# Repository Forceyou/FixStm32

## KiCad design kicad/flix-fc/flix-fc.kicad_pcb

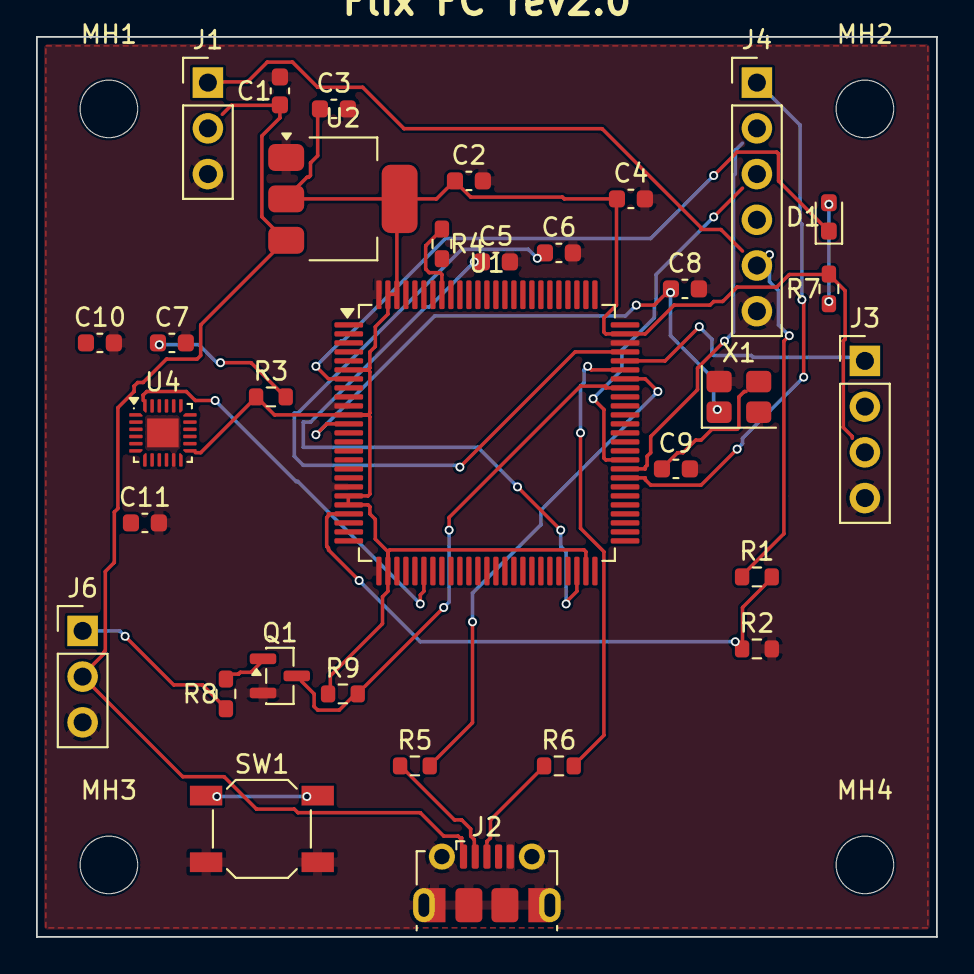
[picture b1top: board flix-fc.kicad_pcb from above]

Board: 2 copper layers, 50.0 x 50.0 mm, 36 parts (0 on the bottom side), 31 nets.

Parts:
C1: 10uF; C_0603_1608Metric
C2: 22uF; C_0603_1608Metric
C3, C4, C7, C10, C11: 100nF; C_0603_1608Metric
C5, C6: 2.2uF; C_0603_1608Metric
C8, C9: 20pF; C_0603_1608Metric
D1: LED; LED_0603_1608Metric
J1: PWR_IN (VBAT/5V/GND); PinHeader_1x03_P2.54mm_Vertical
J2: USB_Micro-B; USB_Micro-B_Molex-105017-0001
J3: SWD; PinHeader_1x04_P2.54mm_Vertical
J4: ESC_OUT; PinHeader_1x06_P2.54mm_Vertical
J6: RC_IN (SBUS/5V/GND); PinHeader_1x03_P2.54mm_Vertical
MH1, MH2, MH3, MH4: M3; MountingHole_3.2mm_M3
Q1: BC847; SOT-23
R1, R3, R4, R8, R9: 10k; R_0603_1608Metric
R2: 3.3k; R_0603_1608Metric
R5, R6: 22R; R_0603_1608Metric
R7: 1k; R_0603_1608Metric
SW1: RESET; SW_SPST_SKQG_WithoutStem
U1: STM32F407VET6; LQFP-100_14x14mm_P0.5mm
U2: AMS1117-3.3; SOT-223-3_TabPin2
U4: MPU9250; QFN-24-1EP_3x3mm_P0.4mm_EP1.75x1.6mm
X1: 8MHz; Crystal_SMD_3225-4Pin_3.2x2.5mm

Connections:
+3V3: C2.1, C3.1, C4.1, C11.1, J3.3, R3.1, R7.2, R9.1, U1.6, U1.11, U1.20, U1.21, U1.27, U1.49, U1.74, U1.98, U1.99, U2.2, U4.8, U4.13
+5V: C1.1, J1.2, J2.1, J6.2, U2.3
+VBAT: J1.1, J4.5, R1.1
BOOT0: R4.1, U1.93
GND: C1.2, C2.2, C3.2, C4.2, C5.2, C6.2, C7.2, C8.2, C9.2, C10.2, C11.2, J1.3, J2.5, J2.SH, J3.4, J4.6, J6.3, Q1.2, R2.2, R4.2, SW1.2, U1.10, U1.19, U1.26, U1.73, U1.100, U2.1, U4.11, U4.18, U4.25, X1.2, X1.4
IMU_CS: U1.3, U4.22
IMU_REGOUT: C10.1, U4.10
LED_A: D1.2, R7.1
LED_STAT: D1.1, U1.7
MOT_FL: J4.4, U1.61
MOT_FR: J4.3, U1.60
MOT_RL: J4.1, U1.58
MOT_RR: J4.2, U1.59
OSC_IN: C8.1, U1.12, X1.1
OSC_OUT: C9.1, U1.13, X1.3
PA11_DM: R5.2, U1.69
PA12_DP: R6.2, U1.70
Q1_B: Q1.1, R8.2
SBUS_IN: J6.1, R8.1
SBUS_RX: Q1.3, R9.2, U1.68
SPI_MISO: U1.30, U4.9
SPI_MOSI: U1.31, U4.24
SPI_SCK: U1.29, U4.23
SWCLK: J3.2, U1.75
SWDIO: J3.1, U1.71
USB_DM: J2.2, R5.1
USB_DP: J2.3, R6.1
VBAT_ADC: R1.2, R2.1, U1.22
VCAP1: C5.1, U1.48
VCAP2: C6.1, U1.72
nRST: C7.1, R3.2, SW1.1, U1.14

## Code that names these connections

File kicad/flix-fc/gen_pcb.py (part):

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    "U1": {"3":"IMU_CS","6":"+3V3","7":"LED_STAT","10":"GND","11":"+3V3","12":"OSC_IN","13":"OSC_OUT",
           "14":"nRST","19":"GND","20":"+3V3","21":"+3V3","22":"VBAT_ADC","26":"GND","27":"+3V3",
           "29":"SPI_SCK","30":"SPI_MISO","31":"SPI_MOSI","48":"VCAP1","49":"+3V3","58":"MOT_RL",
           "59":"MOT_RR","60":"MOT_FR","61":"MOT_FL","68":"SBUS_RX","69":"PA11_DM","70":"PA12_DP",
           "71":"SWDIO","72":"VCAP2","73":"GND","74":"+3V3","75":"SWCLK","93":"BOOT0","98":"+3V3","99":"+3V3","100":"GND"},
    "U4": {"23":"SPI_SCK","24":"SPI_MOSI","9":"SPI_MISO","22":"IMU_CS","12":"IMU_INT","13":"+3V3",
           "8":"+3V3","18":"GND","10":"IMU_REGOUT","11":"GND","25":"GND"},
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    "R2": {"1":"VBAT_ADC","2":"GND"},
    "R3": {"1":"+3V3","2":"nRST"},
    "R4": {"1":"BOOT0","2":"GND"},
    "R5": {"1":"USB_DM","2":"PA11_DM"},
    "R6": {"1":"USB_DP","2":"PA12_DP"},
    "R7": {"1":"LED_A","2":"+3V3"},
    "R8": {"1":"SBUS_IN","2":"Q1_B"},
    "R9": {"1":"+3V3","2":"SBUS_RX"},
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
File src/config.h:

// STM32F407 引脚映射与默认参数
// 基于 STM32F407VET6 开发板 (黑块)

#pragma once

// ===== 电机 PWM 引脚 (TIM4) =====
// TIM4_CH1 ~ TIM4_CH4: PD12 ~ PD15
#define MOT_RL_PIN  PD12   // 后左  (TIM4_CH1)
#define MOT_RR_PIN  PD13   // 后右  (TIM4_CH2)
#define MOT_FR_PIN  PD14   // 前右  (TIM4_CH3)
#define MOT_FL_PIN  PD15   // 前左  (TIM4_CH4)

// ===== IMU SPI 引脚 (SPI1) =====
// GY-91 (MPU9250) / ICM20948
#define IMU_SCK_PIN   PA5    // SPI1_SCK
#define IMU_MISO_PIN  PA6    // SPI1_MISO
#define IMU_MOSI_PIN  PA7    // SPI1_MOSI
#define IMU_CS_PIN    PE4    // 片选
#define IMU_INT_PIN   -1     // 中断脚 (可选, -1 表示使用定时器等待)

// ===== RC SBUS 引脚 (USART1) =====
#define RC_RX_PIN     PA10   // USART1_RX
#define RC_TX_PIN     PA9    // USART1_TX (可选)

// ===== 电池电压 =====
#define VOLTAGE_PIN   PA0    // ADC1_IN0
#define VOLTAGE_SCALE 4.03f  // 分压电阻比 (R上+R下)/R下 = (10k+3.3k)/3.3k

// ===== LED =====
#define LED_PIN       PC13   // 板载蓝色 LED (低电平亮)

// ===== USB 虚拟串口 =====
// STM32F407 的 USB OTG FS 自动映射为 Serial

// ===== 默认参数 =====
void setDefaults() {
    // 电机引脚
    extern int motorPins[4];
    motorPins[MOT_RL] = MOT_RL_PIN;
    motorPins[MOT_RR] = MOT_RR_PIN;
    motorPins[MOT_FR] = MOT_FR_PIN;
    motorPins[MOT_FL] = MOT_FL_PIN;

    // PWM 参数
    extern int pwmFrequency;
    pwmFrequency = 40000;   // 40 kHz (有刷电机推荐)

    // IMU 默认 SPI + MPU9250
    extern int imuModel, imuBus;
    imuModel = 1;   // 1 = MPU9250, 2 = ICM20948, 3 = MPU6050
    imuBus = 0;     // 0 = SPI, 1 = I2C

    extern int imuSckPin, imuMisoPin, imuMosiPin, imuCsPin, imuIntPin;
    imuSckPin  = IMU_SCK_PIN;
    imuMisoPin = IMU_MISO_PIN;
    imuMosiPin = IMU_MOSI_PIN;
    imuCsPin   = IMU_CS_PIN;
    imuIntPin  = IMU_INT_PIN;

    // RC
    extern int rcRxPin;
    rcRxPin = RC_RX_PIN;

    // 电压
    extern int voltagePin;
    extern float voltageScale;
    voltagePin   = VOLTAGE_PIN;
    voltageScale = VOLTAGE_SCALE;
}
